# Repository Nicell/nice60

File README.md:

# This is the old DIY version of the nice!60. This is superseded by a new version, which is fully assembled and much more polished.
# Read more about this new version, and find where to purchase it at https://nicekeyboards.com/nice-60.
## nice60

The nice60 is a hotswap 60% board compatible with Pro Micro footprint boards. This includes the nice!nano, which supports bluetooth.

### BOM
Most parts come from LCSC.

|Qty |Reference(s)   |Value              |LCSC#/Location     |
|----|---------------|-------------------|-------------------|
|61  |D1-D61         |1N4148             |C108804            |
|8   |D62-D69        |WS2812B            |C114586            |
|1   |D70            |SK6812 Mini-E      |Buy from Aliexpress|
|1   |J1             |USB C              |C165948            |
|1   |J3             |JST-PH (battery)   |C173752            |
|61  |MX1-MX61       |Hotswap Sockets    |Buy from KBDFans   |
|2   |R2, R3         |5.1k               |C304897            |
|1   |SW1            |Reset Switch       |C388295            |
|1   |U2             |USB ESD Protection |C7519              |
|1   |Stabilizers    |4x2u 1x6.25u       |Buy from KBDFans   |
|6/12|N/A            |M2x7mm Standoffs   |Buy from Aliexpress|
|1   |USB Cable      |Match Pro Micro USB|Anywhere           |

### PCB

There are three gerber zips for PCBs.

1. pcb_gerbers.zip - The actual PCB gerbers
2. plate_gerbers.zip - The top plate for the board
3. backplate_gerbers.zip - The bottom case/plate for the board

These can be bought from JLCPCB the cheapest.

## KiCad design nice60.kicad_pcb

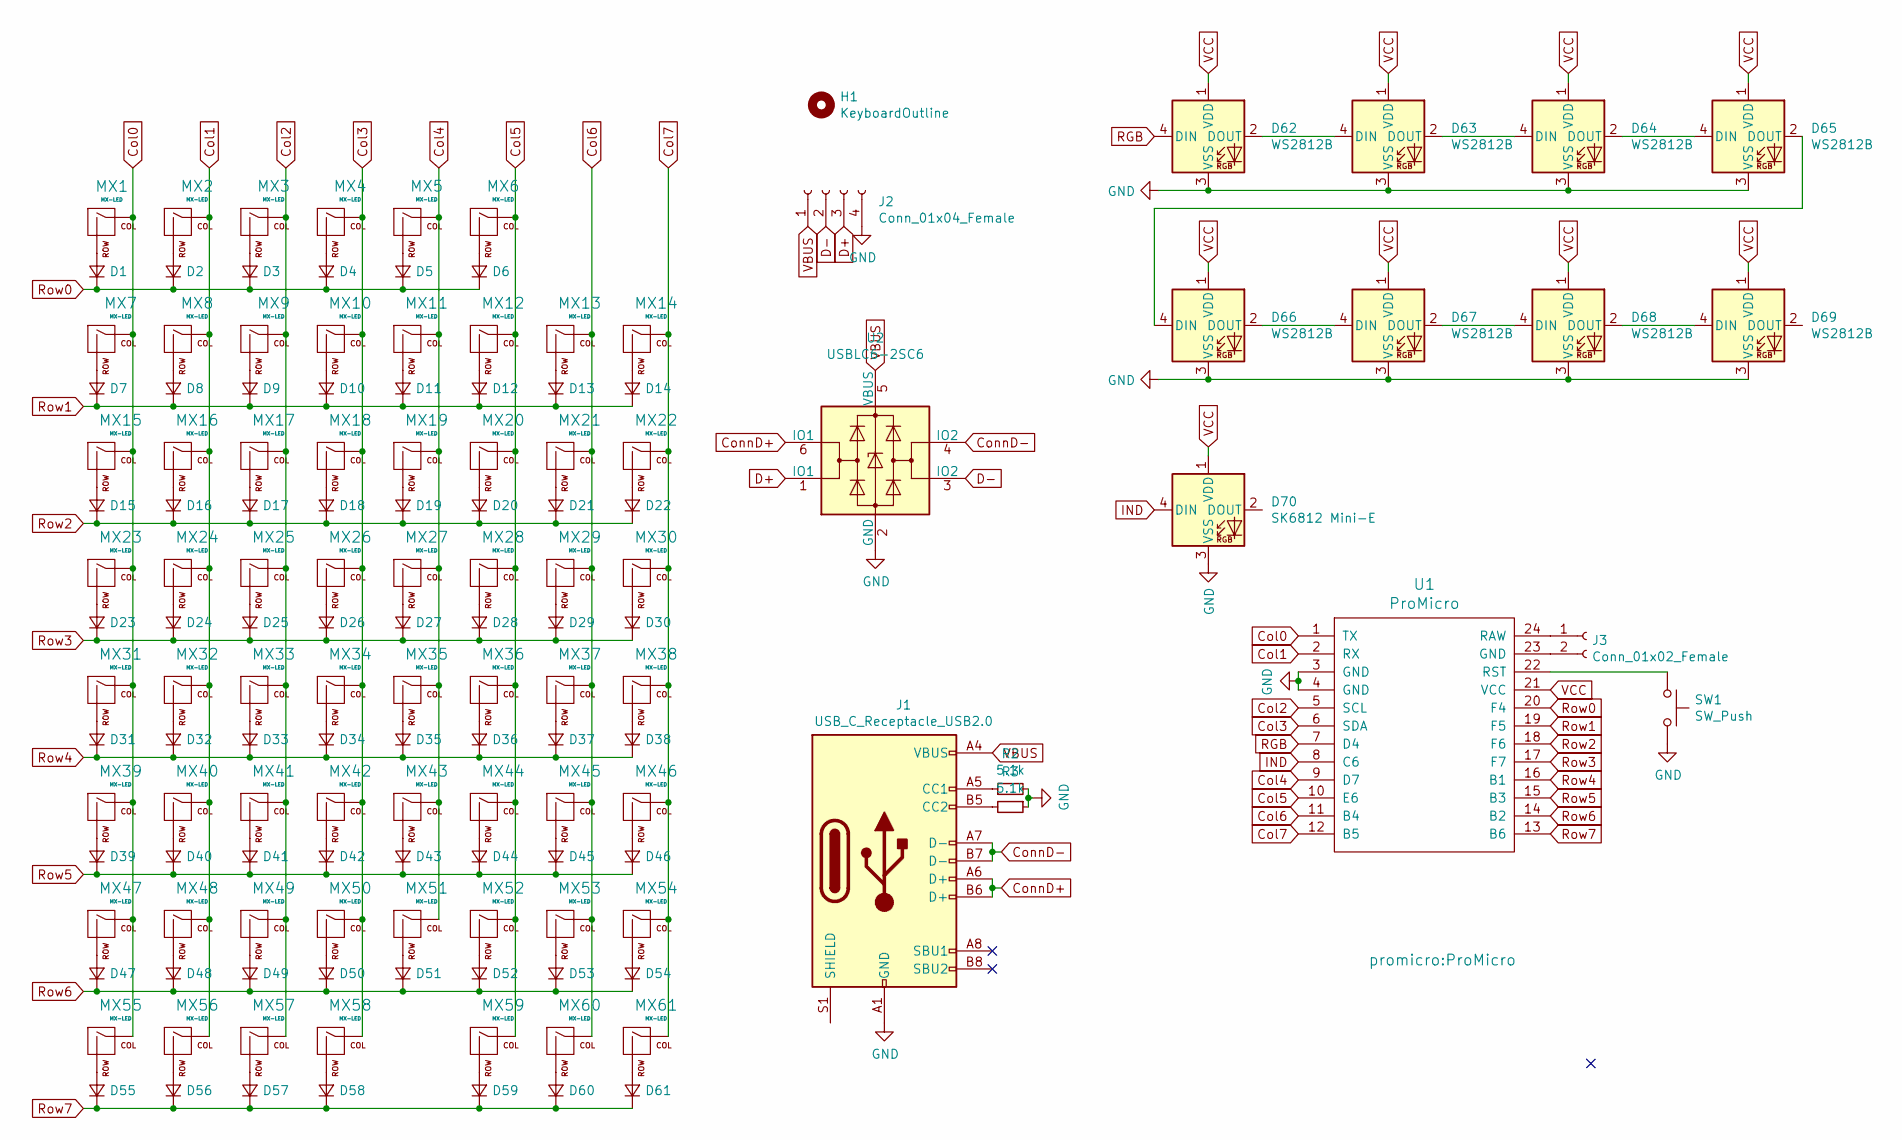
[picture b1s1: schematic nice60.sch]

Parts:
D1, D2, D3, D4, D5, D6, D7, D8, D9, D10, D11, D12, D13, D14, D15, D16, D17, D18, D19, D20, D21, D22, D23, D24, D25, D26, D27, D28, D29, D30, D31, D32, D33, D34, D35, D36, D37, D38, D39, D40, D41, D42, D43, D44, D45, D46, D47, D48, D49, D50, D51, D52, D53, D54, D55, D56, D57, D58, D59, D60, D61: D_Small; D_SOD-123; LCSC C108804
D62, D63, D64, D65, D66, D67, D68, D69: WS2812B; LED_WS2812B_PLCC4_5.0x5.0mm_P3.2mm; LCSC C114586
D70: SK6812 Mini-E; SK6812Mini-E
H1: KeyboardOutline; 60_Outline-Modded-Type-C
J1: USB_C_Receptacle_USB2.0; HRO-TYPE-C-31-M-12-HandSoldering; LCSC C165948
J2: Conn_01x04_Female; PinSocket_1x04_P2.54mm_Vertical
J3: Conn_01x02_Female; JST_PH_S2B-PH-K_1x02_P2.00mm_Horizontal; LCSC C173752
MX1, MX2, MX3, MX4, MX5, MX6, MX7, MX8, MX9, MX10, MX11, MX12, MX13, MX15, MX16, MX17, MX18, MX19, MX20, MX21, MX22, MX23, MX24, MX25, MX26, MX27, MX28, MX29, MX32, MX33, MX34, MX35, MX36, MX37, MX40, MX41, MX42, MX43, MX44, MX45, MX48, MX49, MX50, MX51, MX52, MX53: MX-LED; MXOnly-1U-Hotswap
MX14: MX-LED; MXOnly-2U-Hotswap
MX30, MX31: MX-LED; MXOnly-1.5U-Hotswap
MX38, MX47: MX-LED; MXOnly-2.25U-Hotswap
MX39: MX-LED; MXOnly-1.75U-Hotswap
MX46: MX-LED; MXOnly-2.75U-Hotswap
MX54, MX55, MX56, MX57, MX59, MX60, MX61: MX-LED; MXOnly-1.25U-Hotswap
MX58: MX-LED; MXOnly-6.25U-Hotswap-ReversedStabilizers
R2, R3: 5.1k; R_1206_3216Metric_Pad1.42x1.75mm_HandSolder; LCSC C304897
SW1: SW_Push; SW_SPST_TL3342; LCSC C388295
U1: ProMicro
U2: USBLC6-2SC6; SOT-23-6; LCSC C7519

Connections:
Col0: MX1.1 (COL), MX7.1 (COL), MX15.1 (COL), MX23.1 (COL), MX31.1 (COL), MX39.1 (COL), MX47.1 (COL), MX55.1 (COL), U1.1 (TX)
Col1: MX2.1 (COL), MX8.1 (COL), MX16.1 (COL), MX24.1 (COL), MX32.1 (COL), MX40.1 (COL), MX48.1 (COL), MX56.1 (COL), U1.2 (RX)
Col2: MX3.1 (COL), MX9.1 (COL), MX17.1 (COL), MX25.1 (COL), MX33.1 (COL), MX41.1 (COL), MX49.1 (COL), MX57.1 (COL), U1.5 (SCL)
Col3: MX4.1 (COL), MX10.1 (COL), MX18.1 (COL), MX26.1 (COL), MX34.1 (COL), MX42.1 (COL), MX50.1 (COL), MX58.1 (COL), U1.6 (SDA)
Col4: MX5.1 (COL), MX11.1 (COL), MX19.1 (COL), MX27.1 (COL), MX35.1 (COL), MX43.1 (COL), MX51.1 (COL), U1.9 (D7)
Col5: MX6.1 (COL), MX12.1 (COL), MX20.1 (COL), MX28.1 (COL), MX36.1 (COL), MX44.1 (COL), MX52.1 (COL), MX59.1 (COL), U1.10 (E6)
Col6: MX13.1 (COL), MX21.1 (COL), MX29.1 (COL), MX37.1 (COL), MX45.1 (COL), MX53.1 (COL), MX60.1 (COL), U1.11 (B4)
Col7: MX14.1 (COL), MX22.1 (COL), MX30.1 (COL), MX38.1 (COL), MX46.1 (COL), MX54.1 (COL), MX61.1 (COL), U1.12 (B5)
ConnD+: J1.A6 (D+), J1.B6 (D+), U2.6 (IO1)
ConnD-: J1.A7 (D-), J1.B7 (D-), U2.4 (IO2)
D+: J2.3, U2.1 (IO1)
D-: J2.2, U2.3 (IO2)
GND: D62.3 (VSS), D63.3 (VSS), D64.3 (VSS), D65.3 (VSS), D66.3 (VSS), D67.3 (VSS), D68.3 (VSS), D69.3 (VSS), D70.3 (VSS), J1.A1 (GND), J1.A12 (GND), J1.B1 (GND), J1.B12 (GND), J2.4, R2.2, R3.1, SW1.2, U1.3 (GND), U1.4 (GND), U2.2 (GND)
IND: D70.4 (DIN), U1.8 (C6)
unnamed: D1.2 (A), MX1.2 (ROW)
unnamed: D2.2 (A), MX2.2 (ROW)
unnamed: D3.2 (A), MX3.2 (ROW)
unnamed: D4.2 (A), MX4.2 (ROW)
unnamed: D5.2 (A), MX5.2 (ROW)
unnamed: D6.2 (A), MX6.2 (ROW)
unnamed: D7.2 (A), MX7.2 (ROW)
unnamed: D8.2 (A), MX8.2 (ROW)
unnamed: D9.2 (A), MX9.2 (ROW)
unnamed: D10.2 (A), MX10.2 (ROW)
unnamed: D11.2 (A), MX11.2 (ROW)
unnamed: D12.2 (A), MX12.2 (ROW)
unnamed: D13.2 (A), MX13.2 (ROW)
unnamed: D14.2 (A), MX14.2 (ROW)
unnamed: D15.2 (A), MX15.2 (ROW)
unnamed: D16.2 (A), MX16.2 (ROW)
unnamed: D17.2 (A), MX17.2 (ROW)
unnamed: D18.2 (A), MX18.2 (ROW)
unnamed: D19.2 (A), MX19.2 (ROW)
unnamed: D20.2 (A), MX20.2 (ROW)
unnamed: D21.2 (A), MX21.2 (ROW)
unnamed: D22.2 (A), MX22.2 (ROW)
unnamed: D23.2 (A), MX23.2 (ROW)
unnamed: D24.2 (A), MX24.2 (ROW)
unnamed: D25.2 (A), MX25.2 (ROW)
unnamed: D26.2 (A), MX26.2 (ROW)
unnamed: D27.2 (A), MX27.2 (ROW)
unnamed: D28.2 (A), MX28.2 (ROW)
unnamed: D29.2 (A), MX29.2 (ROW)
unnamed: D30.2 (A), MX30.2 (ROW)
unnamed: D31.2 (A), MX31.2 (ROW)
unnamed: D32.2 (A), MX32.2 (ROW)
unnamed: D33.2 (A), MX33.2 (ROW)
unnamed: D34.2 (A), MX34.2 (ROW)
unnamed: D35.2 (A), MX35.2 (ROW)
unnamed: D36.2 (A), MX36.2 (ROW)
unnamed: D37.2 (A), MX37.2 (ROW)
unnamed: D38.2 (A), MX38.2 (ROW)
unnamed: D39.2 (A), MX39.2 (ROW)
unnamed: D40.2 (A), MX40.2 (ROW)
unnamed: D41.2 (A), MX41.2 (ROW)
unnamed: D42.2 (A), MX42.2 (ROW)
unnamed: D43.2 (A), MX43.2 (ROW)
unnamed: D44.2 (A), MX44.2 (ROW)
unnamed: D45.2 (A), MX45.2 (ROW)
unnamed: D46.2 (A), MX46.2 (ROW)
unnamed: D47.2 (A), MX47.2 (ROW)
unnamed: D48.2 (A), MX48.2 (ROW)
unnamed: D49.2 (A), MX49.2 (ROW)
unnamed: D50.2 (A), MX50.2 (ROW)
unnamed: D51.2 (A), MX51.2 (ROW)
unnamed: D52.2 (A), MX52.2 (ROW)
unnamed: D53.2 (A), MX53.2 (ROW)
unnamed: D54.2 (A), MX54.2 (ROW)
unnamed: D55.2 (A), MX55.2 (ROW)
unnamed: D56.2 (A), MX56.2 (ROW)
unnamed: D57.2 (A), MX57.2 (ROW)
unnamed: D58.2 (A), MX58.2 (ROW)
unnamed: D59.2 (A), MX59.2 (ROW)
unnamed: D60.2 (A), MX60.2 (ROW)
unnamed: D61.2 (A), MX61.2 (ROW)
unnamed: D62.2 (DOUT), D63.4 (DIN)
unnamed: D63.2 (DOUT), D64.4 (DIN)
unnamed: D64.2 (DOUT), D65.4 (DIN)
unnamed: D65.2 (DOUT), D66.4 (DIN)
unnamed: D66.2 (DOUT), D67.4 (DIN)
unnamed: D67.2 (DOUT), D68.4 (DIN)
unnamed: D68.2 (DOUT), D69.4 (DIN)
unnamed: J1.A5 (CC1), R2.1
unnamed: J1.B5 (CC2), R3.2
unnamed 88: J3.1, U1.24 (RAW); also elsewhere on the board
unnamed 89: J3.2, U1.23 (GND); also elsewhere on the board
unnamed: SW1.1, U1.22 (RST)
RGB: D62.4 (DIN), U1.7 (D4)
Row0: D1.1 (K), D2.1 (K), D3.1 (K), D4.1 (K), D5.1 (K), D6.1 (K), U1.20 (F4)
Row1: D7.1 (K), D8.1 (K), D9.1 (K), D10.1 (K), D11.1 (K), D12.1 (K), D13.1 (K), D14.1 (K), U1.19 (F5)
Row2: D15.1 (K), D16.1 (K), D17.1 (K), D18.1 (K), D19.1 (K), D20.1 (K), D21.1 (K), D22.1 (K), U1.18 (F6)
Row3: D23.1 (K), D24.1 (K), D25.1 (K), D26.1 (K), D27.1 (K), D28.1 (K), D29.1 (K), D30.1 (K), U1.17 (F7)
Row4: D31.1 (K), D32.1 (K), D33.1 (K), D34.1 (K), D35.1 (K), D36.1 (K), D37.1 (K), D38.1 (K), U1.16 (B1)
Row5: D39.1 (K), D40.1 (K), D41.1 (K), D42.1 (K), D43.1 (K), D44.1 (K), D45.1 (K), D46.1 (K), U1.15 (B3)
Row6: D47.1 (K), D48.1 (K), D49.1 (K), D50.1 (K), D51.1 (K), D52.1 (K), D53.1 (K), D54.1 (K), U1.14 (B2)
Row7: D55.1 (K), D56.1 (K), D57.1 (K), D58.1 (K), D59.1 (K), D60.1 (K), D61.1 (K), U1.13 (B6)
VBUS: J1.A4 (VBUS), J1.A9 (VBUS), J1.B4 (VBUS), J1.B9 (VBUS), J2.1, U2.5 (VBUS)
VCC: D62.1 (VDD), D63.1 (VDD), D64.1 (VDD), D65.1 (VDD), D66.1 (VDD), D67.1 (VDD), D68.1 (VDD), D69.1 (VDD), D70.1 (VDD), U1.21 (VCC)

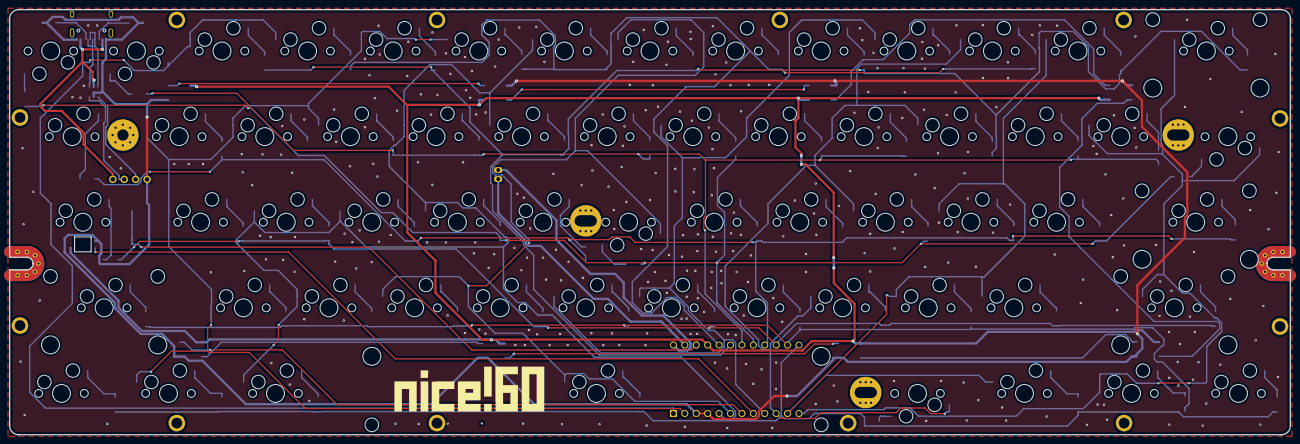
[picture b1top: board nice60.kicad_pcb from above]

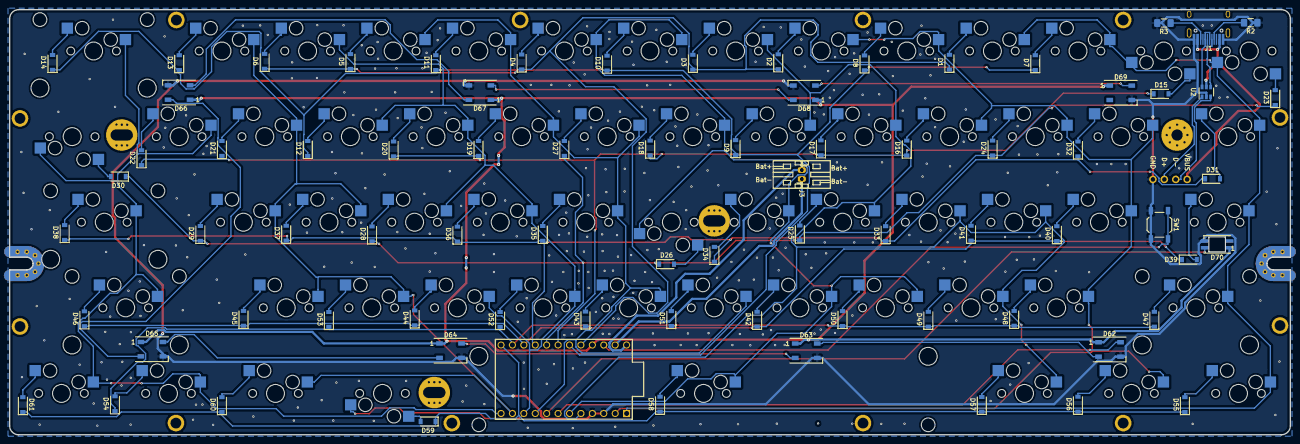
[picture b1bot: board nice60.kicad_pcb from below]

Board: 2 copper layers, 285.0 x 94.6 mm, 141 parts (77 on the bottom side), 98 nets.

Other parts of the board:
J3#2: Conn_01x02_Female; JST_PH_S2B-PH-K_1x02_P2.00mm_Horizontal

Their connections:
unnamed 88: J3#2.1; also elsewhere on the board
unnamed 89: J3#2.2; also elsewhere on the board

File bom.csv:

"Item","Qty","Reference(s)","Value","LibPart","Footprint","Datasheet","LCSC"
"1","61","D1, D2, D3, D4, D5, D6, D7, D8, D9, D10, D11, D12, D13, D14, D15, D16, D17, D18, D19, D20, D21, D22, D23, D24, D25, D26, D27, D28, D29, D30, D31, D32, D33, D34, D35, D36, D37, D38, D39, D40, D41, D42, D43, D44, D45, D46, D47, D48, D49, D50, D51, D52, D53, D54, D55, D56, D57, D58, D59, D60, D61","D_Small","Device:D_Small","Diode_SMD:D_SOD-123","~","C108804"
"2","8","D62, D63, D64, D65, D66, D67, D68, D69","WS2812B","LED:WS2812B","LED_SMD:LED_WS2812B_PLCC4_5.0x5.0mm_P3.2mm","https://cdn-shop.adafruit.com/datasheets/WS2812B.pdf","C114586"
"3","1","D70","SK6812 Mini-E","LED:WS2812B","nice60:SK6812Mini-E","https://cdn-shop.adafruit.com/datasheets/WS2812B.pdf","Buy from Aliexpress"
"5","1","J1","USB_C_Receptacle_USB2.0","Connector:USB_C_Receptacle_USB2.0","Type-C:HRO-TYPE-C-31-M-12-HandSoldering","https://www.usb.org/sites/default/files/documents/usb_type-c.zip","C165948"
"7","1","J3","Conn_01x02_Female","Connector:Conn_01x02_Female","Connector_JST:JST_PH_S2B-PH-K_1x02_P2.00mm_Horizontal","~","C173752"
"8","61","MX1, MX2, MX3, MX4, MX5, MX6, MX7, MX8, MX9, MX10, MX11, MX12, MX13, MX14, MX15, MX16, MX17, MX18, MX19, MX20, MX21, MX22, MX23, MX24, MX25, MX26, MX27, MX28, MX29, MX30, MX31, MX32, MX33, MX34, MX35, MX36, MX37, MX38, MX39, MX40, MX41, MX42, MX43, MX44, MX45, MX46, MX47, MX48, MX49, MX50, MX51, MX52, MX53, MX54, MX55, MX56, MX57, MX58, MX59, MX60, MX61","MX-LED","MX_Alps_Hybrid:MX-NoLED","MX_Only:MXOnly-1U-Hotswap","","Buy from KBDFans"
"16","2","R2, R3","5.1k","Device:R_Small","Resistor_SMD:R_1206_3216Metric_Pad1.42x1.75mm_HandSolder","~","C304897"
"17","1","SW1","SW_Push","Switch:SW_Push","Button_Switch_SMD:SW_SPST_TL3342","~","C388295"
"19","1","U2","USBLC6-2SC6","Power_Protection:USBLC6-2SC6","Package_TO_SOT_SMD:SOT-23-6","http://www2.st.com/resource/en/datasheet/CD00050750.pdf","C7519"

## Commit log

2020-05-30 Add files
2020-06-01 Fix plate to have solder mask and 3mm thick edges
2020-06-08 Fix VBUS connection to ESD protection
2020-06-13 Add better JST connector silkscreen
2021-04-28 Notice of new nice!60 being released.
2021-07-24 Improve fluency
